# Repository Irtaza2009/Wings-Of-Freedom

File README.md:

# Wings Of Freedom Keychain

A keychain with the **Wings of Freedom** (the Scout Regiment emblem) from **Attack on Titan**!

## 3d View

## Schematic

## PCB

Lights up in the dark using a photoresistor!

## BOM
- 2 LED (Blue + White)
- 2 NPN Transistor
- 1 Photoresistor
- 1 47k Resistor
- 2 220 Resistor
- 1 10k Resistor
- 1 1k Resistor
- 1 Battery Holder
- 1 Push Button
- 1 Vibrating Motor
- 1 Diode

Made by @Irtaza for the [Solder YSWS](http://solder.hackclub.com/)!

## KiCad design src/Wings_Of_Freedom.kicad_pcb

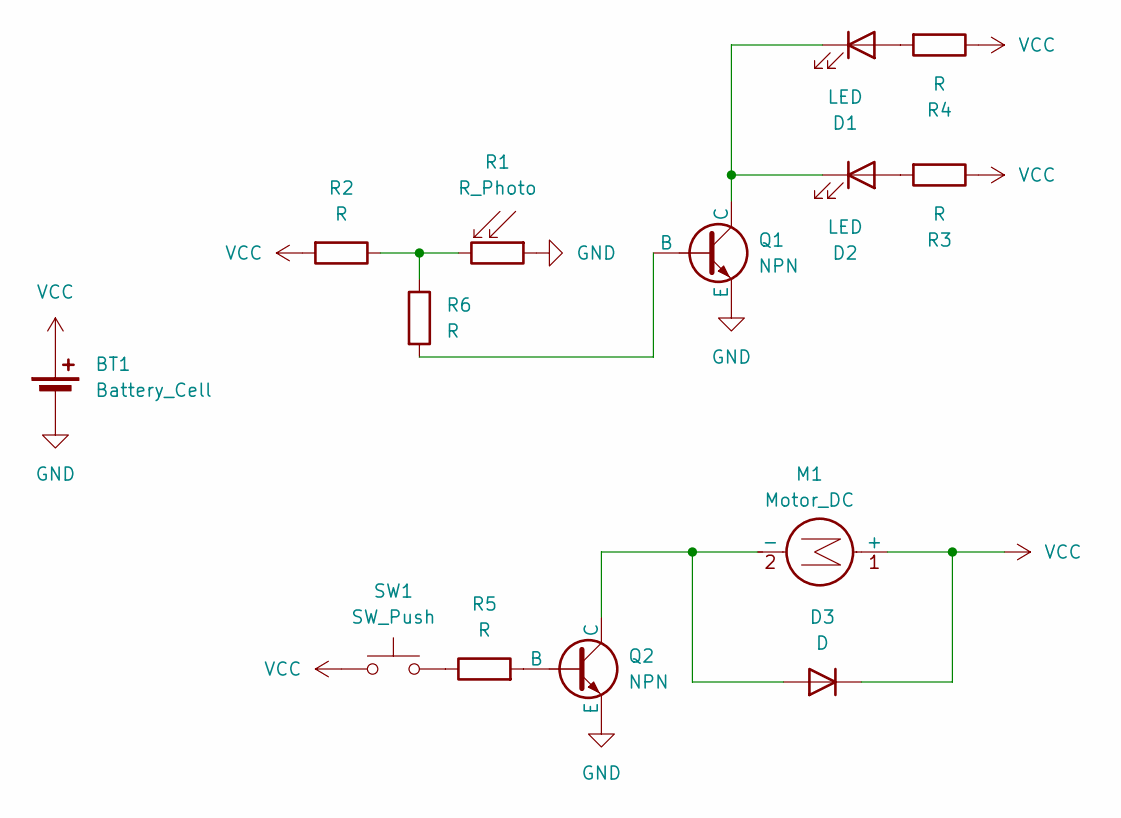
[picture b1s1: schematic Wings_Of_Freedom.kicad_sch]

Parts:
BT1: Battery_Cell; BatteryHolder_Keystone_3034_1x20mm
D1, D2: LED; LED_D5.0mm
D3: D; D_DO-35_SOD27_P7.62mm_Horizontal
M1: Motor_DC; PinHeader_1x02_P2.54mm_Vertical
Q1, Q2: NPN; TO-92L_HandSolder
R1: R_Photo; R_LDR_5.1x4.3mm_P3.4mm_Vertical
R2, R3, R4, R5, R6: R; R_Axial_DIN0207_L6.3mm_D2.5mm_P7.62mm_Horizontal
SW1: SW_Push; SW_PUSH_6mm

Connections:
GND: BT1.2 (-), Q1.3 (E), Q2.3 (E), R1.1
unnamed: D1.2 (A), R4.2
unnamed: D1.1 (K), D2.1 (K), Q1.1 (C)
unnamed: D2.2 (A), R3.2
unnamed: D3.2 (A), M1.2 (-), Q2.1 (C)
unnamed: Q1.2 (B), R6.2
unnamed: Q2.2 (B), R5.2
unnamed: R1.2, R2.1, R6.1
unnamed: R5.1, SW1.2
VCC: BT1.1 (+), D3.1 (K), M1.1 (+), R2.2, R3.1, R4.1, SW1.1

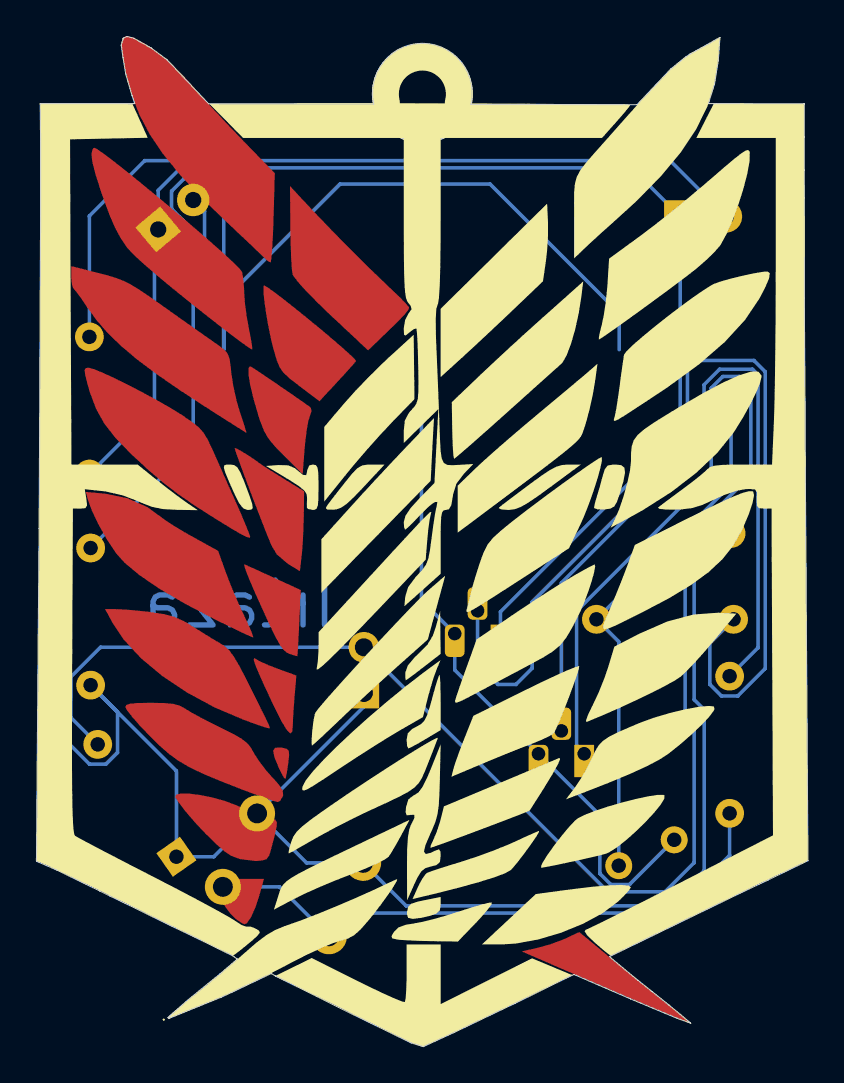
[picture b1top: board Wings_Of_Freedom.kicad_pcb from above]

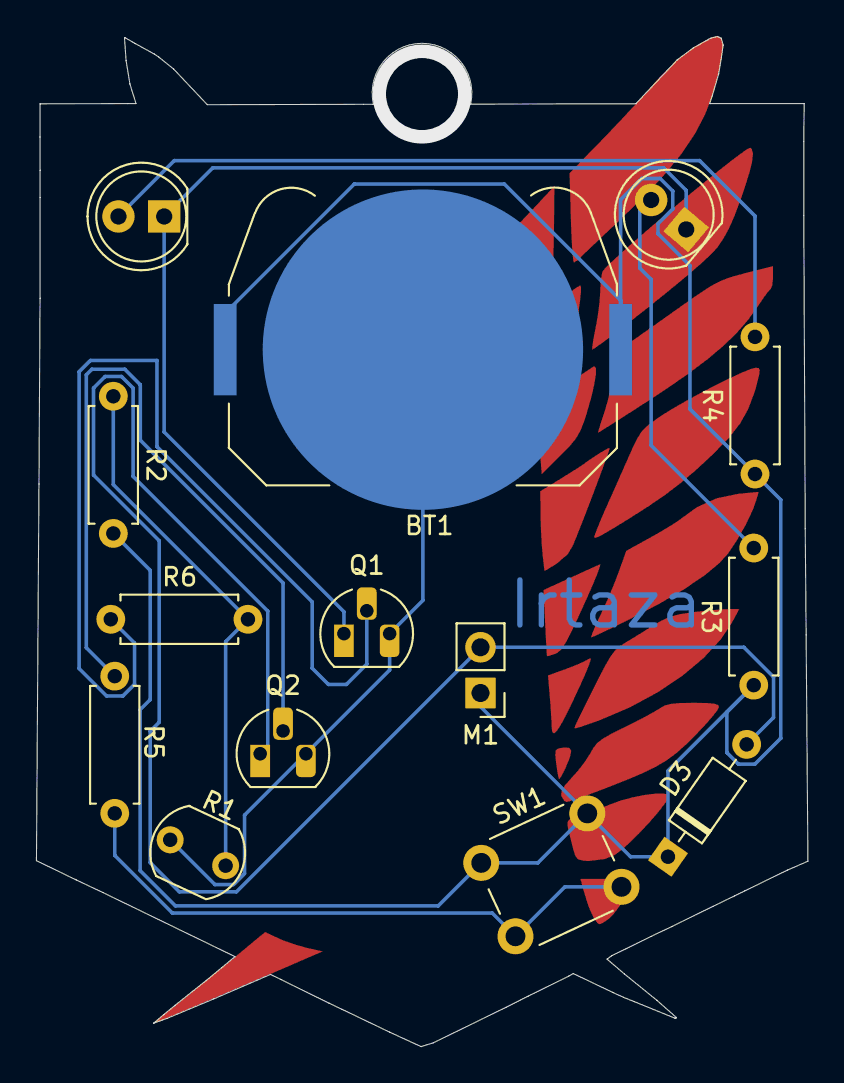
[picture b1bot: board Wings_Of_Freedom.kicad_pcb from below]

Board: 2 copper layers, 42.9 x 56.1 mm, 15 parts (14 on the bottom side), 10 nets.

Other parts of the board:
White: Outline_W

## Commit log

2025-05-25 Added Source files
2025-05-26 Added gerbers and drill file!
2025-05-26 Updated gerbers + drill files!
2025-05-26 Added updated gerbers + drill files!
